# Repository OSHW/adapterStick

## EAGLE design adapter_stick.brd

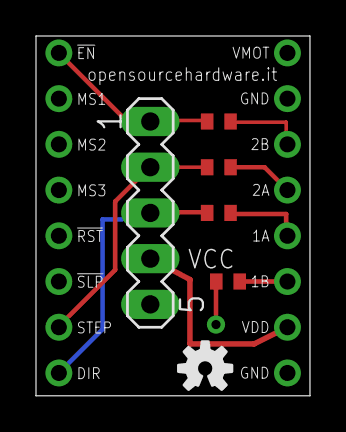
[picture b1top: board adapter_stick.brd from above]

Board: 2 copper layers, 15.2 x 20.0 mm, 7 parts (0 on the bottom side), 9 nets.

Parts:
J1X: CLONOLU
R2: EN; R0402
R3: DIR; R0402
R4: STEP; R0402
R5: GND; R0402
SV1: MA05-1
U$1: OSHW-LOGO-S

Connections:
2A: J1X.2A, R3.2
DIR: J1X.DIR, R4.1, SV1.3
EN: J1X.!EN, R2.1, SV1.1
GND: J1X.GND$1, J1X.GND$2, R5.1, SV1.5
unnamed: J1X.1B, R5.2
unnamed: J1X.1A, R4.2
unnamed: J1X.2B, R2.2
NC: J1X.STEP, R3.1, SV1.2
VDD: J1X.VDD, SV1.4

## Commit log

2015-02-23 :lollipop: Added .gitattributes & .gitignore files
2015-03-03 silkscreen update
2015-03-09 BUG in board (DIR jumper shorted)

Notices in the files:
parts and their libraries:
SparkFun-Aesthetics: Licensing: Creative Commons ShareAlike 4.0 International - https://creativecommons.org/licenses/by-sa/4.0
